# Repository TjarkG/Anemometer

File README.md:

# Anemometer

Ultrasonic Anemometer based on an cheap distance Sensors

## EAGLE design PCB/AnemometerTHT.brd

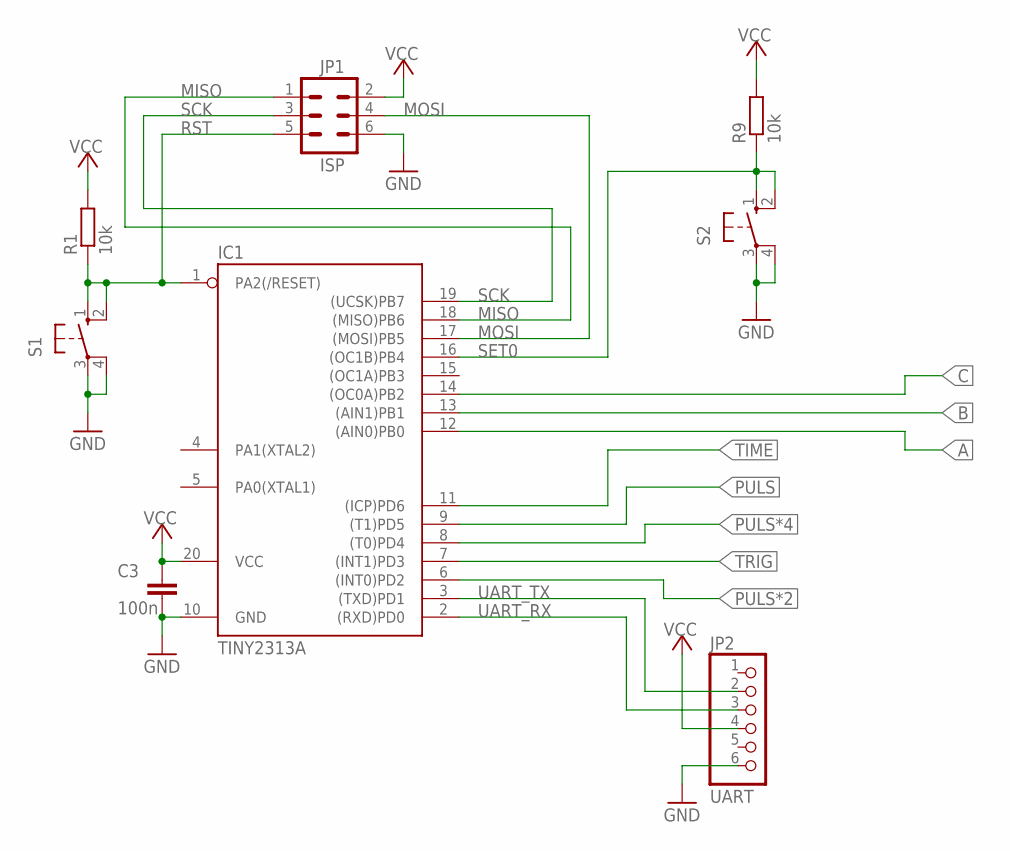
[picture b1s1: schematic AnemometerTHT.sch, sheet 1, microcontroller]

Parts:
C3: 100n; C050-030X075
IC1: TINY2313A; DIL20
JP1: ISP; ML6
JP2: UART; 1X06
R1, R9: 10k; 0204/7
S1, S2: 10-XX; B3F-10XX

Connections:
A: IC1.12 ((AIN0)PB0); also elsewhere on the board
B: IC1.13 ((AIN1)PB1); also elsewhere on the board
C: IC1.14 ((OC0A)PB2); also elsewhere on the board
GND: C3.2, IC1.10 (GND), JP1.6, JP2.6, S1.3, S1.4 (P1), S2.3, S2.4 (P1); also elsewhere on the board
MISO: IC1.18 ((MISO)PB6), JP1.1
MOSI: IC1.17 ((MOSI)PB5), JP1.4
PULS: IC1.9 ((T1)PD5); also elsewhere on the board
PULS*2: IC1.6 ((INT0)PD2); also elsewhere on the board
PULS*4: IC1.8 ((T0)PD4); also elsewhere on the board
RST: IC1.1 (PA2(/RESET)), JP1.5, R1.1, S1.1 (S), S1.2 (S1)
SCK: IC1.19 ((UCSK)PB7), JP1.3
SET0: IC1.16 ((OC1B)PB4), R9.1, S2.1 (S), S2.2 (S1)
TIME: IC1.11 ((ICP)PD6); also elsewhere on the board
TRIG: IC1.7 ((INT1)PD3); also elsewhere on the board
UART_RX: IC1.2 ((RXD)PD0), JP2.3
UART_TX: IC1.3 ((TXD)PD1), JP2.2
VCC: C3.1, IC1.20 (VCC), JP1.2, JP2.4, R1.2, R9.2; also elsewhere on the board

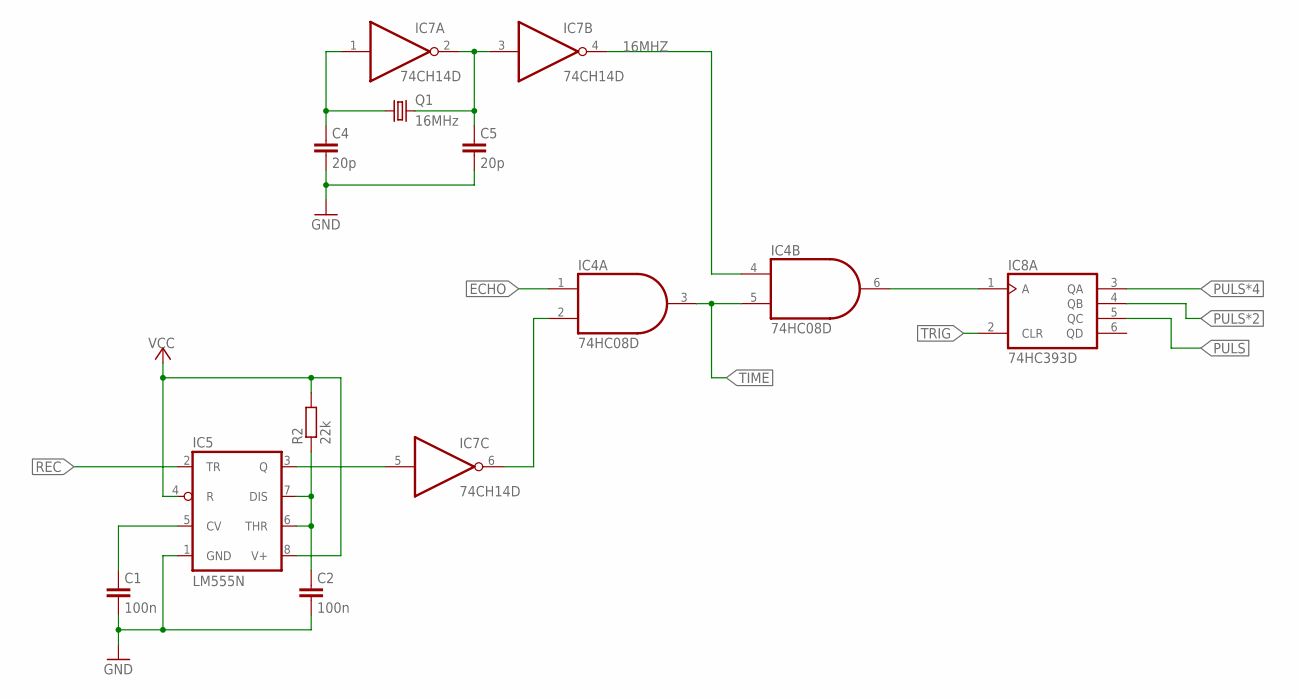
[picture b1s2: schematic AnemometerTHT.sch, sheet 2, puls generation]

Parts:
C1, C2: 100n; C050-030X075
C4, C5: 20p; C050-030X075
IC4: 74HC08D; DIL14
IC5: LM555N; DIL08
IC7: 74CH14D; DIL14
IC8: 74HC393D; DIL14
Q1: 16MHz; HC49U70
R2: 22k; 0204/7

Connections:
16MHZ: IC4.4 (I0), IC7.4 (O)
ECHO: IC4.1 (I0); also elsewhere on the board
GND: C1.2, C2.2, C4.2, C5.2, IC5.1 (GND); also elsewhere on the board
unnamed: IC5.3 (Q), IC7.5 (I)
unnamed: C1.1, IC5.5 (CV)
unnamed: IC4.6 (O), IC8.1 (A)
unnamed: C2.1, IC5.6 (THR), IC5.7 (DIS), R2.1
unnamed: IC4.2 (I1), IC7.6 (O)
unnamed: C4.1, IC7.1 (I), Q1.1
unnamed: C5.1, IC7.2 (O), IC7.3 (I), Q1.2
PULS: IC8.5 (QC); also elsewhere on the board
PULS*2: IC8.4 (QB); also elsewhere on the board
PULS*4: IC8.3 (QA); also elsewhere on the board
REC: IC5.2 (TR); also elsewhere on the board
TIME: IC4.3 (O), IC4.5 (I1); also elsewhere on the board
TRIG: IC8.2 (CLR); also elsewhere on the board
VCC: IC5.4 (R), IC5.8 (V+), R2.2; also elsewhere on the board

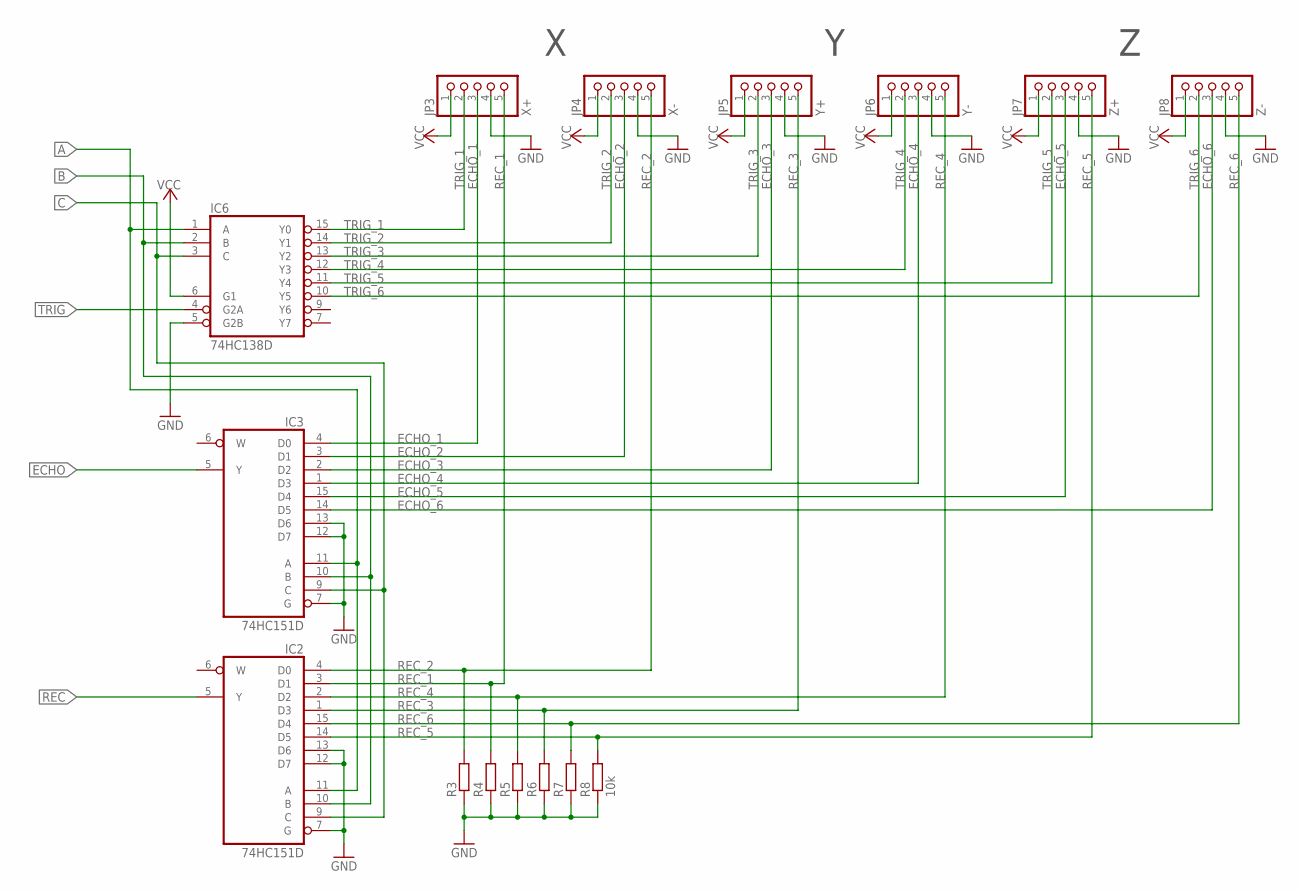
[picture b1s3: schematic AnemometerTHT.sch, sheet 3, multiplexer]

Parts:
IC2, IC3: 74HC151D; DIL16
IC6: 74HC138D; DIL16
JP3: X+; 1X05
JP4: X-; 1X05
JP5: Y+; 1X05
JP6: Y-; 1X05
JP7: Z+; 1X05
JP8: Z-; 1X05
R3, R4, R5, R6, R7, R8: 10k; 0204/7

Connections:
A: IC2.11 (A), IC3.11 (A), IC6.1 (A); also elsewhere on the board
B: IC2.10 (B), IC3.10 (B), IC6.2 (B); also elsewhere on the board
C: IC2.9 (C), IC3.9 (C), IC6.3 (C); also elsewhere on the board
ECHO: IC3.5 (Y); also elsewhere on the board
ECHO_1: IC3.4 (D0), JP3.3
ECHO_2: IC3.3 (D1), JP4.3
ECHO_3: IC3.2 (D2), JP5.3
ECHO_4: IC3.1 (D3), JP6.3
ECHO_5: IC3.15 (D4), JP7.3
ECHO_6: IC3.14 (D5), JP8.3
GND: IC2.7 (G), IC2.12 (D7), IC2.13 (D6), IC3.7 (G), IC3.12 (D7), IC3.13 (D6), IC6.5 (G2B), JP3.4, JP4.4, JP5.4, JP6.4, JP7.4, JP8.4, R3.1, R4.1, R5.1, R6.1, R7.1, R8.1; also elsewhere on the board
REC: IC2.5 (Y); also elsewhere on the board
REC_1: IC2.3 (D1), JP3.5, R4.2
REC_2: IC2.4 (D0), JP4.5, R3.2
REC_3: IC2.1 (D3), JP5.5, R6.2
REC_4: IC2.2 (D2), JP6.5, R5.2
REC_5: IC2.14 (D5), JP7.5, R8.2
REC_6: IC2.15 (D4), JP8.5, R7.2
TRIG: IC6.4 (G2A); also elsewhere on the board
TRIG_1: IC6.15 (Y0), JP3.2
TRIG_2: IC6.14 (Y1), JP4.2
TRIG_3: IC6.13 (Y2), JP5.2
TRIG_4: IC6.12 (Y3), JP6.2
TRIG_5: IC6.11 (Y4), JP7.2
TRIG_6: IC6.10 (Y5), JP8.2
VCC: IC6.6 (G1), JP3.1, JP4.1, JP5.1, JP6.1, JP7.1, JP8.1; also elsewhere on the board

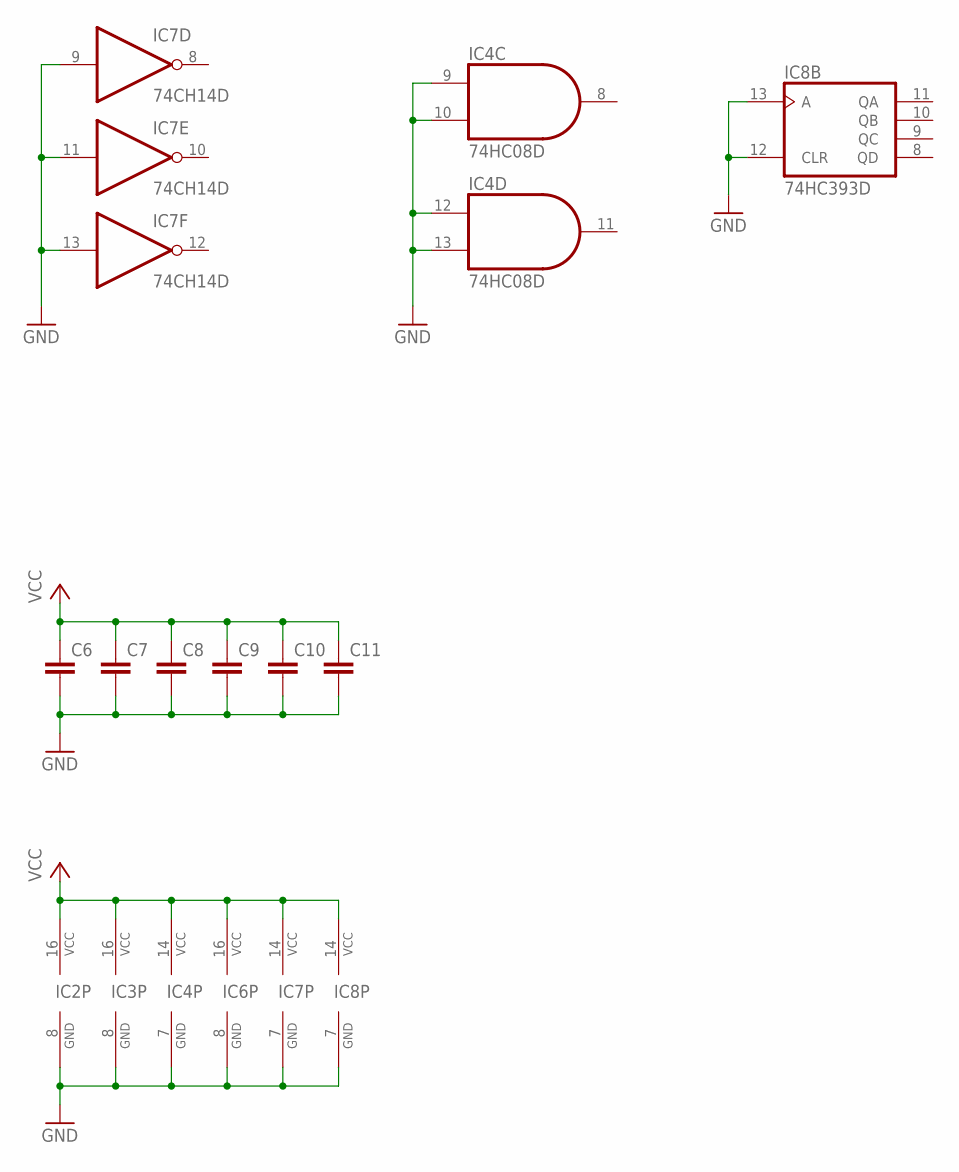
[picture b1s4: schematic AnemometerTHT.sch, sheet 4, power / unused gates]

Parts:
C6, C7, C8, C9, C10, C11: C-EU050-030X075; C050-030X075
IC2, IC3: 74HC151D; DIL16
IC4: 74HC08D; DIL14
IC6: 74HC138D; DIL16
IC7: 74CH14D; DIL14
IC8: 74HC393D; DIL14

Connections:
GND: C6.2, C7.2, C8.2, C9.2, C10.2, C11.2, IC2.8 (GND), IC3.8 (GND), IC4.7 (GND), IC4.9 (I0), IC4.10 (I1), IC4.12 (I0), IC4.13 (I1), IC6.8 (GND), IC7.7 (GND), IC7.9 (I), IC7.11 (I), IC7.13 (I), IC8.7 (GND), IC8.12 (CLR), IC8.13 (A); also elsewhere on the board
VCC: C6.1, C7.1, C8.1, C9.1, C10.1, C11.1, IC2.16 (VCC), IC3.16 (VCC), IC4.14 (VCC), IC6.16 (VCC), IC7.14 (VCC), IC8.14 (VCC); also elsewhere on the board

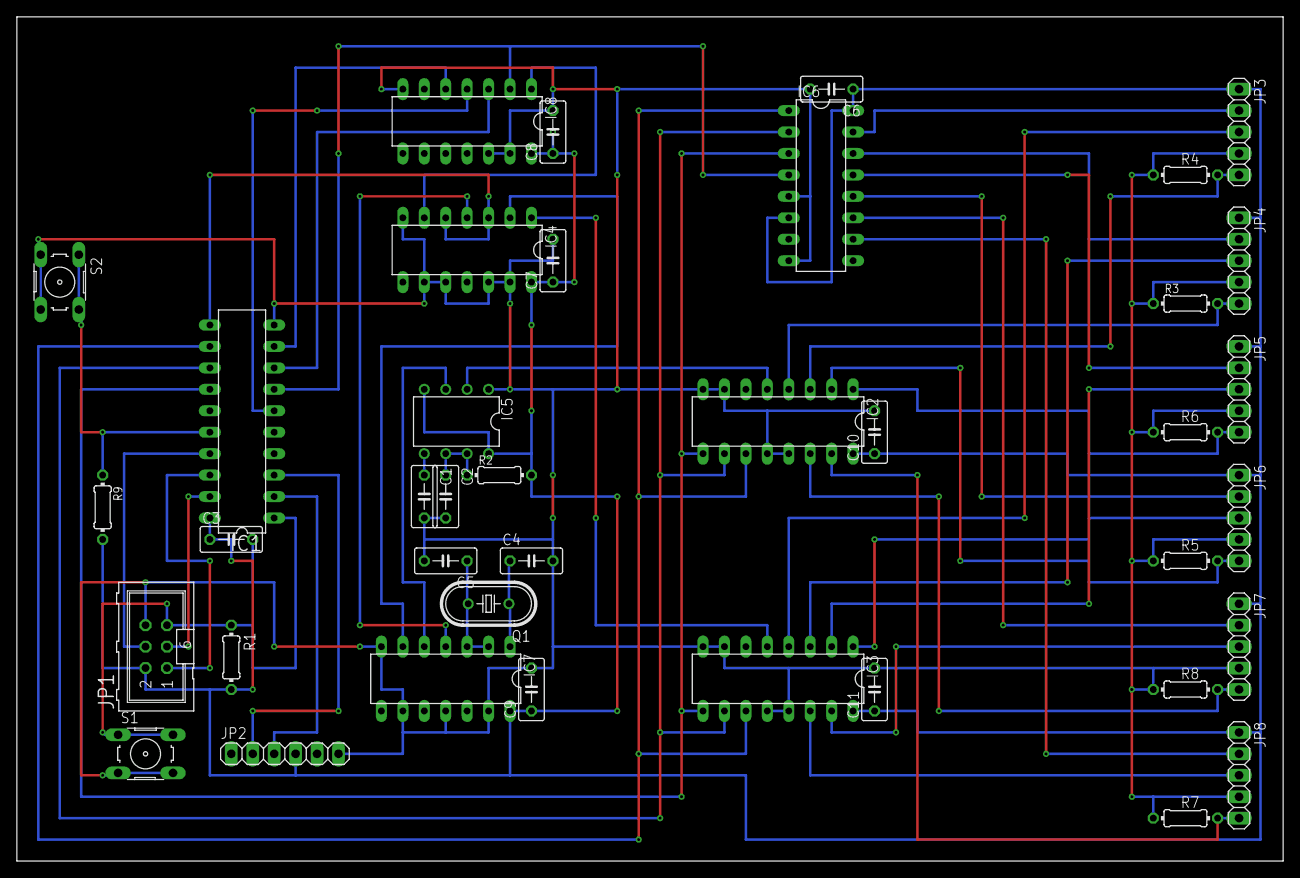
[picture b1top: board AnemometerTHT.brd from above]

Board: 2 copper layers, 150.0 x 100.0 mm, 39 parts (0 on the bottom side), 45 nets.

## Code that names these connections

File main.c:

/*
 * main.c for ultrasonic anemometer
 *
 * Created: 22.11.2021 13:52
 * Author : tjark
 * Target : Anemometer.sch
 * 
 * Fuses: 
 * avrdude -U lfuse:w:0xff:m -U hfuse:w:0x9b:m -U efuse:w:0xff:m -c avrispmkII -p attiny2313
 */

#ifndef __AVR_ATtiny2313A__
#define __AVR_ATtiny2313A__
#endif

#define F_CPU       16000000UL
#define S_SENSOR    200         //Distance betwen Sensors in mm
#define Nr_Sens     1           //Number of Sensors connected
#define Nr_Med      128         //Number of readings used when setting offset
#define ASCII                   //Comment out for raw output

#define TIME    (PIND & (1 << 6))
#define PULS    (PIND & (1 << 5))
#define PULS2   (PIND & (1 << 2))
#define PULS4   (PIND & (1 << 4))
#define ECHO    (PINB & (1 << 3))
#define TRIG_PORT PORTD
#define TRIG_PIN PIND3

#define SET0    (PINB & (1 << 4))

#define writeOfs(adr, value)    eeprom_write_word((uint16_t*) (unsigned int) (adr), (value) )
#define readOfs(i)              ((int) eeprom_read_word((uint16_t*) (unsigned int) (i)))

#include <avr/io.h>
#include <avr/interrupt.h>
#include <avr/eeprom.h>
#include <util/delay.h>
#include "HC_SR04.h"
#include "uart.h"

void setAdr(char adr);
int velocity(unsigned int t1, unsigned int t2);

int main(void)
{
    DDRD = (1 << 1) | (1 << 3);
    DDRB = (1 << 0) | (1 << 1) | (1 << 2);
    PORTB |= (1 << PINB4);
    uartInit();
    start_Timer_1();        //Timer for Messuring Sensor Delay
    setAdr(0);

    while(1)
    {
        int time;
        time = getSensorTime();
        uartWriteIntLine(time);
    }
}

void setAdr(char adr)
{
    unsigned char tmp = PINB;
    tmp &= ~(0x07);
    tmp |= ((!!(adr & (1<<2))) << 0) | ((!!(adr & (1<<1))) << 1) | ((!!(adr & (1<<0))) << 2);
    PORTB = tmp;
}

int velocity(unsigned int t1, unsigned int t2)  //returns velocity in cm/s
{
    return ((S_SENSOR*(F_CPU/100))/t1) - ((S_SENSOR*(F_CPU/100))/t2);
}

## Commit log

2021-11-22 added basic filestructure and HC_SR04 library for Distance messurment
2021-11-22 corrected header
2021-11-22 changed sorting algorithm to quicksort
2021-11-23 added Sensor Time Function
2021-11-24 added velocity output
2021-11-24 added UART Header and Schematic
2021-11-28 added Houskeeping to Schematic
2021-11-28 made getTime work
2021-11-30 adjustet output compensation Formular
2021-12-02 changed timekeeping to hardware timer
2021-12-03 changed to only messure echo puls
2021-12-03 moved edge detection to ISR
2021-12-03 moved ECHO to ICP
2021-12-03 simplyfied ISR
2021-12-03 removed unnecesary functions
2021-12-03 removed unnecesarry functions
2021-12-04 added input Logic to Schematic
2021-12-04 added clock out
2021-12-04 changed messurment methode to half external counter
2021-12-05 added timeout protection
2021-12-05 messured ticks for different differences
2021-12-06 added mean function
2021-12-06 added THT variant with board
2021-12-11 added quartz
2021-12-12 added resistors to make clock run reliable
2021-12-19 moved pcb files into folder
2021-12-20 adjusted code to hardware
2021-12-22 realized that i inverted the wrong signal
2021-12-22 added setAdr
2021-12-23 changed code to read out multiple sensors
2021-12-23 made compiler happy about signing
2021-12-23 corrected multilexer addressing
2021-12-25 added velocity calculation
2021-12-26 made printing negatives possible
2021-12-27 added offset corection
2021-12-27 moved offsets to eeprom
2021-12-27 fixed missing word
2021-12-27 adjusted code to work with non human reciver
2021-12-27 changed output to raw bytes
2021-12-27 removed outdated schematic
2021-12-28 added ASCII Output Mode
2021-12-28 moved puls counter to in/4
2022-01-07 added Distance Header
2022-01-11 added model of Sensor Case
